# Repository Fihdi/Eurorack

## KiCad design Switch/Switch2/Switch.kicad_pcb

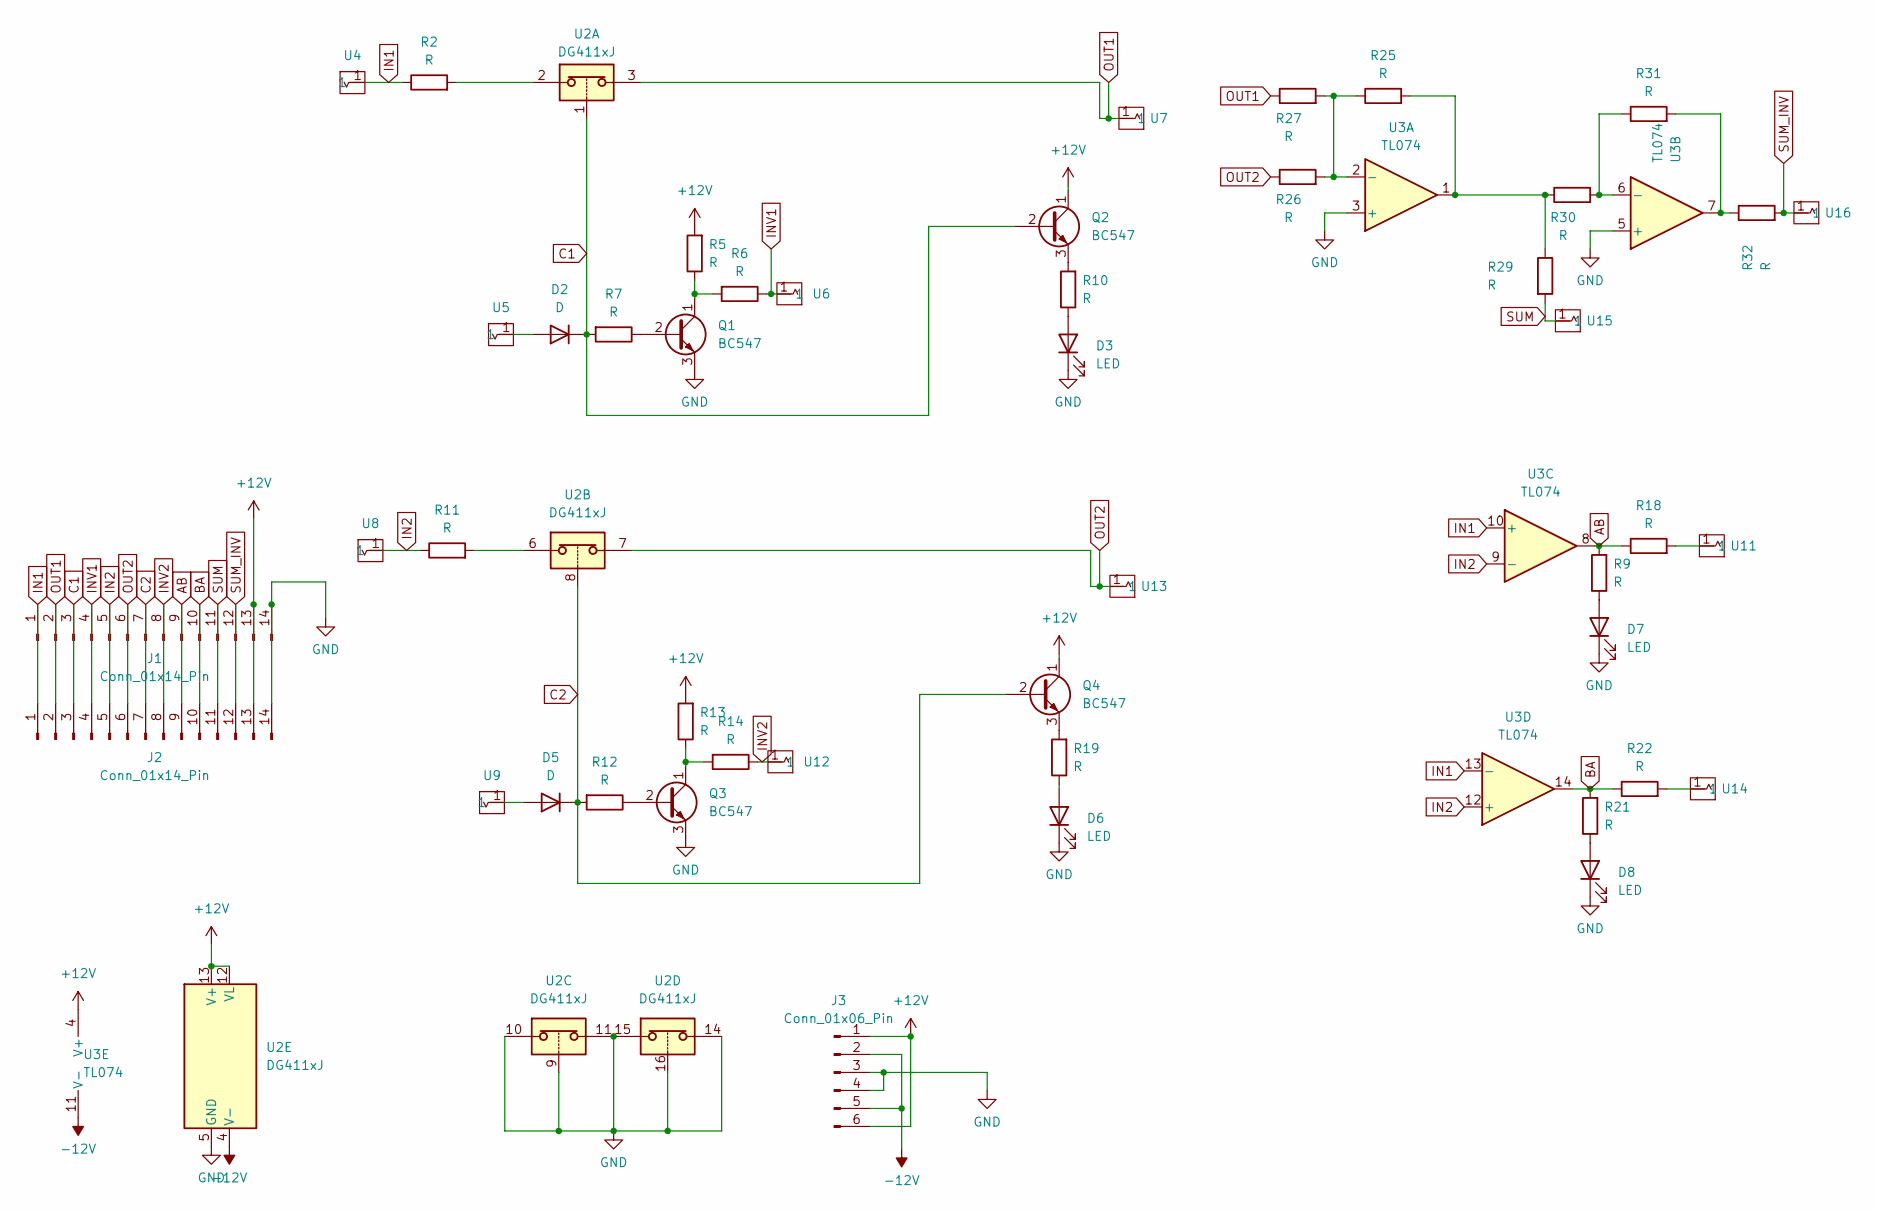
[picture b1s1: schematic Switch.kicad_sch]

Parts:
D2, D5: D; D_DO-34_SOD68_P5.08mm_Vertical_AnodeUp
D3, D6, D7, D8: LED; LED_D3.0mm
J1, J2: Conn_01x14_Pin; PinHeader_1x14_P2.54mm_Vertical
J3: Conn_01x06_Pin; PinHeader_1x06_P2.54mm_Vertical
Q1, Q2, Q3, Q4: BC547; TO-92L_Wide
R2, R5, R6, R7, R9, R10, R11, R12, R13, R14, R18, R19, R21, R22, R25, R26, R27, R29, R30, R31, R32: R; R_Axial_DIN0207_L6.3mm_D2.5mm_P7.62mm_Horizontal
U2: DG411xJ; DIP-16_W7.62mm
U3: TL074; DIP-14_W7.62mm_Socket
U4, U5, U6, U7, U8, U9, U11, U12, U13, U14, U15, U16: Aux_flush; aux_flush

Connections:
+12V: J1.13, J2.13, J3.1, J3.6, Q2.1 (C), Q4.1 (C), R5.2, R13.2, U2.12 (VL), U2.13 (V+), U3.4 (V+)
-12V: J3.2, J3.5, U2.4 (V-), U3.11 (V-)
AB: J1.9, J2.9, R9.2, R18.1, U3.8
BA: J1.10, J2.10, R21.2, R22.1, U3.14
C1: D2.1 (K), J1.3, J2.3, Q2.2 (B), R7.2, U2.1
C2: D5.1 (K), J1.7, J2.7, Q4.2 (B), R12.2, U2.8
GND: D3.1 (K), D6.1 (K), D7.1 (K), D8.1 (K), J1.14, J2.14, J3.3, J3.4, Q1.3 (E), Q3.3 (E), U2.5 (GND), U2.9, U2.10, U2.11, U2.14, U2.15, U2.16, U3.3 (+), U3.5 (+)
IN1: J1.1, J2.1, R2.1, U3.10 (+), U3.13 (-), U4.1
IN2: J1.5, J2.5, R11.1, U3.9 (-), U3.12 (+), U8.1
INV1: J1.4, J2.4, R6.1, U6.1
INV2: J1.8, J2.8, R14.1, U12.1
unnamed: D2.2 (A), U5.1
unnamed: D3.2 (A), R10.1
unnamed: D5.2 (A), U9.1
unnamed: D6.2 (A), R19.1
unnamed: D7.2 (A), R9.1
unnamed: D8.2 (A), R21.1
unnamed: Q1.2 (B), R7.1
unnamed: Q1.1 (C), R5.1, R6.2
unnamed: Q2.3 (E), R10.2
unnamed: Q3.2 (B), R12.1
unnamed: Q3.1 (C), R13.1, R14.2
unnamed: Q4.3 (E), R19.2
unnamed: R2.2, U2.2
unnamed: R11.2, U2.6
unnamed: R18.2, U11.1
unnamed: R22.2, U14.1
unnamed: R25.2, R29.1, R30.1, U3.1
unnamed: R31.2, R32.1, U3.7
unnamed: R25.1, R26.2, R27.2, U3.2 (-)
unnamed: R30.2, R31.1, U3.6 (-)
OUT1: J1.2, J2.2, R27.1, U2.3, U7.1
OUT2: J1.6, J2.6, R26.1, U2.7, U13.1
SUM: J1.11, J2.11, R29.2, U15.1
SUM_INV: J1.12, J2.12, R32.2, U16.1

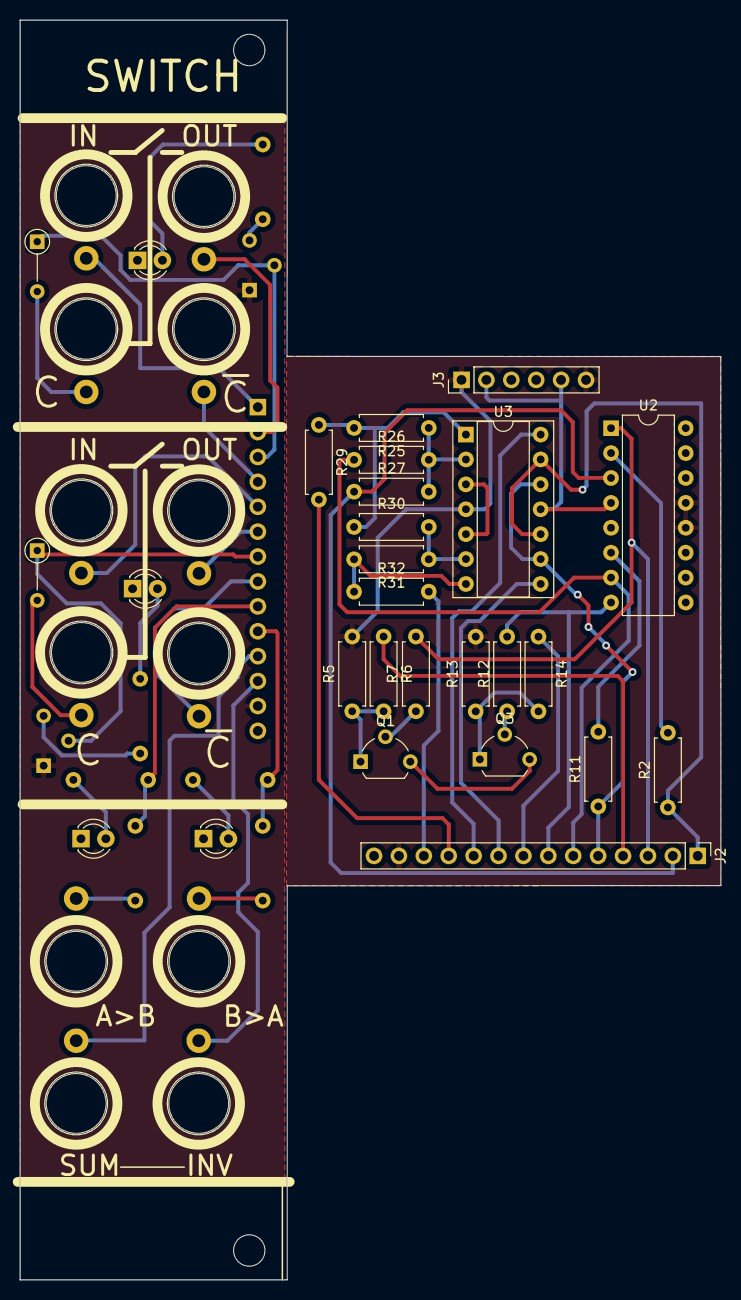
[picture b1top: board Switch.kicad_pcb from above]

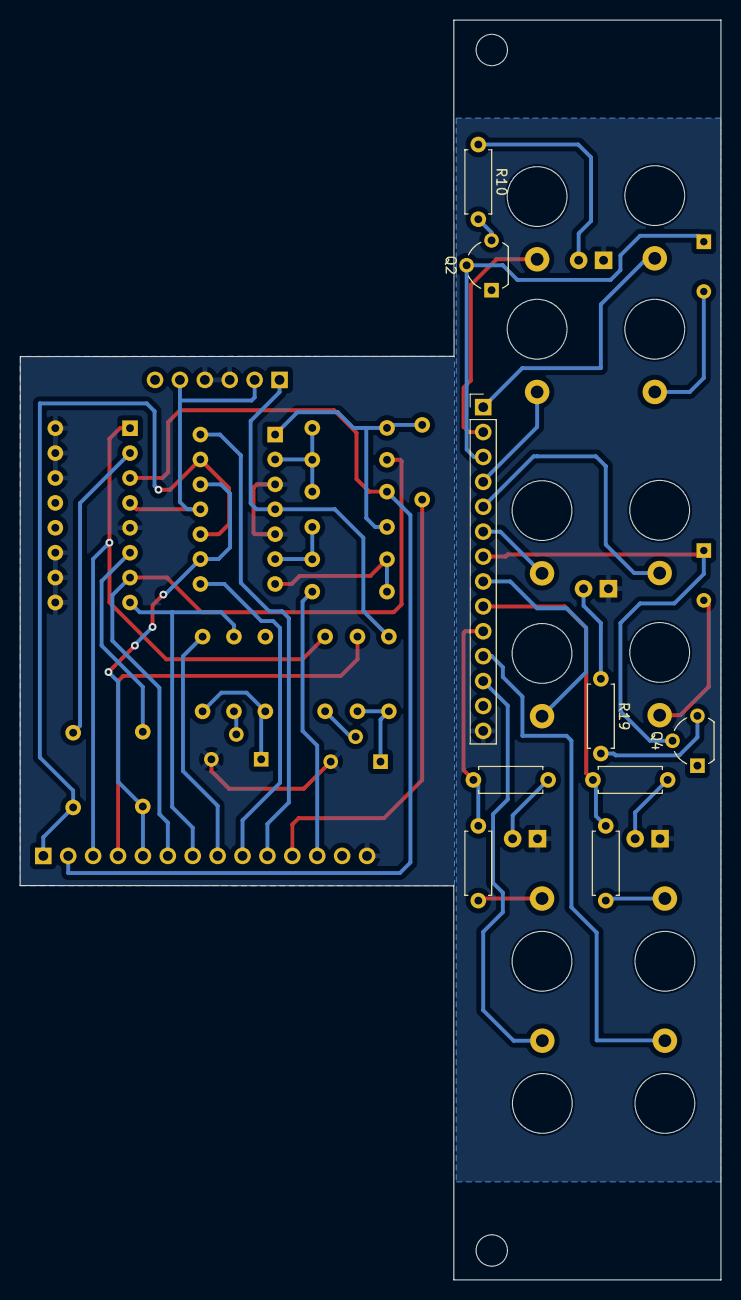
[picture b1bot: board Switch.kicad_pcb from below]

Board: 2 copper layers, 71.5 x 128.5 mm, 48 parts (9 on the bottom side), 35 nets.

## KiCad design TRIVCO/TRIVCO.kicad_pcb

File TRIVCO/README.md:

It is a beefed up relaxation oscillator using an inverting schmitt trigger. See: https://en.wikipedia.org/wiki/Relaxation_oscillator. The charging resistor has been replaced by an LM13700 trans-conductance amplifier (OTA), acting as a CCCS. The control voltages are summed through two inverting amplifiers with unity gain and sent to an exponential current converter that controls the OTA's output current (And thus the frequency). Tuning the exponential current converter is crucial to get proper Volt per Octave tracking.

The capacitor voltage is buffered and DC offset is removed (triangle/saw output), that voltage is compared to either ground or to an external voltage leveled to approx. 5V and buffered once again (pwm output).

The SYNCH input features a schmitt trigger input with small hysteresis (~100mV) to prevent spontaneous syncing from noise. For signals substantialy bigger than 100mV this schmitt trigger acts as a zero-crossing comparator; Whose output is fed to the schmitt trigger junction of the oscillator, achieving synchronisation by averaging the two schmitt triggers outputs together.

Minor issues:
-No trimpots for 1V/Oct tracking

-Triangle signal after the buffer is shifted up/down by the schmitt trigger for synchronisation -> comparator compares this signal to ground -> duty cylce is not 50% at default. This should be easily fixable by adding a decoupling cap in series to R14, or by bypassing the comparator alltogether and connecting the 100k resistor directly to the SYNCH input

-LED is mostly usless excpet when using the module as an LFO.

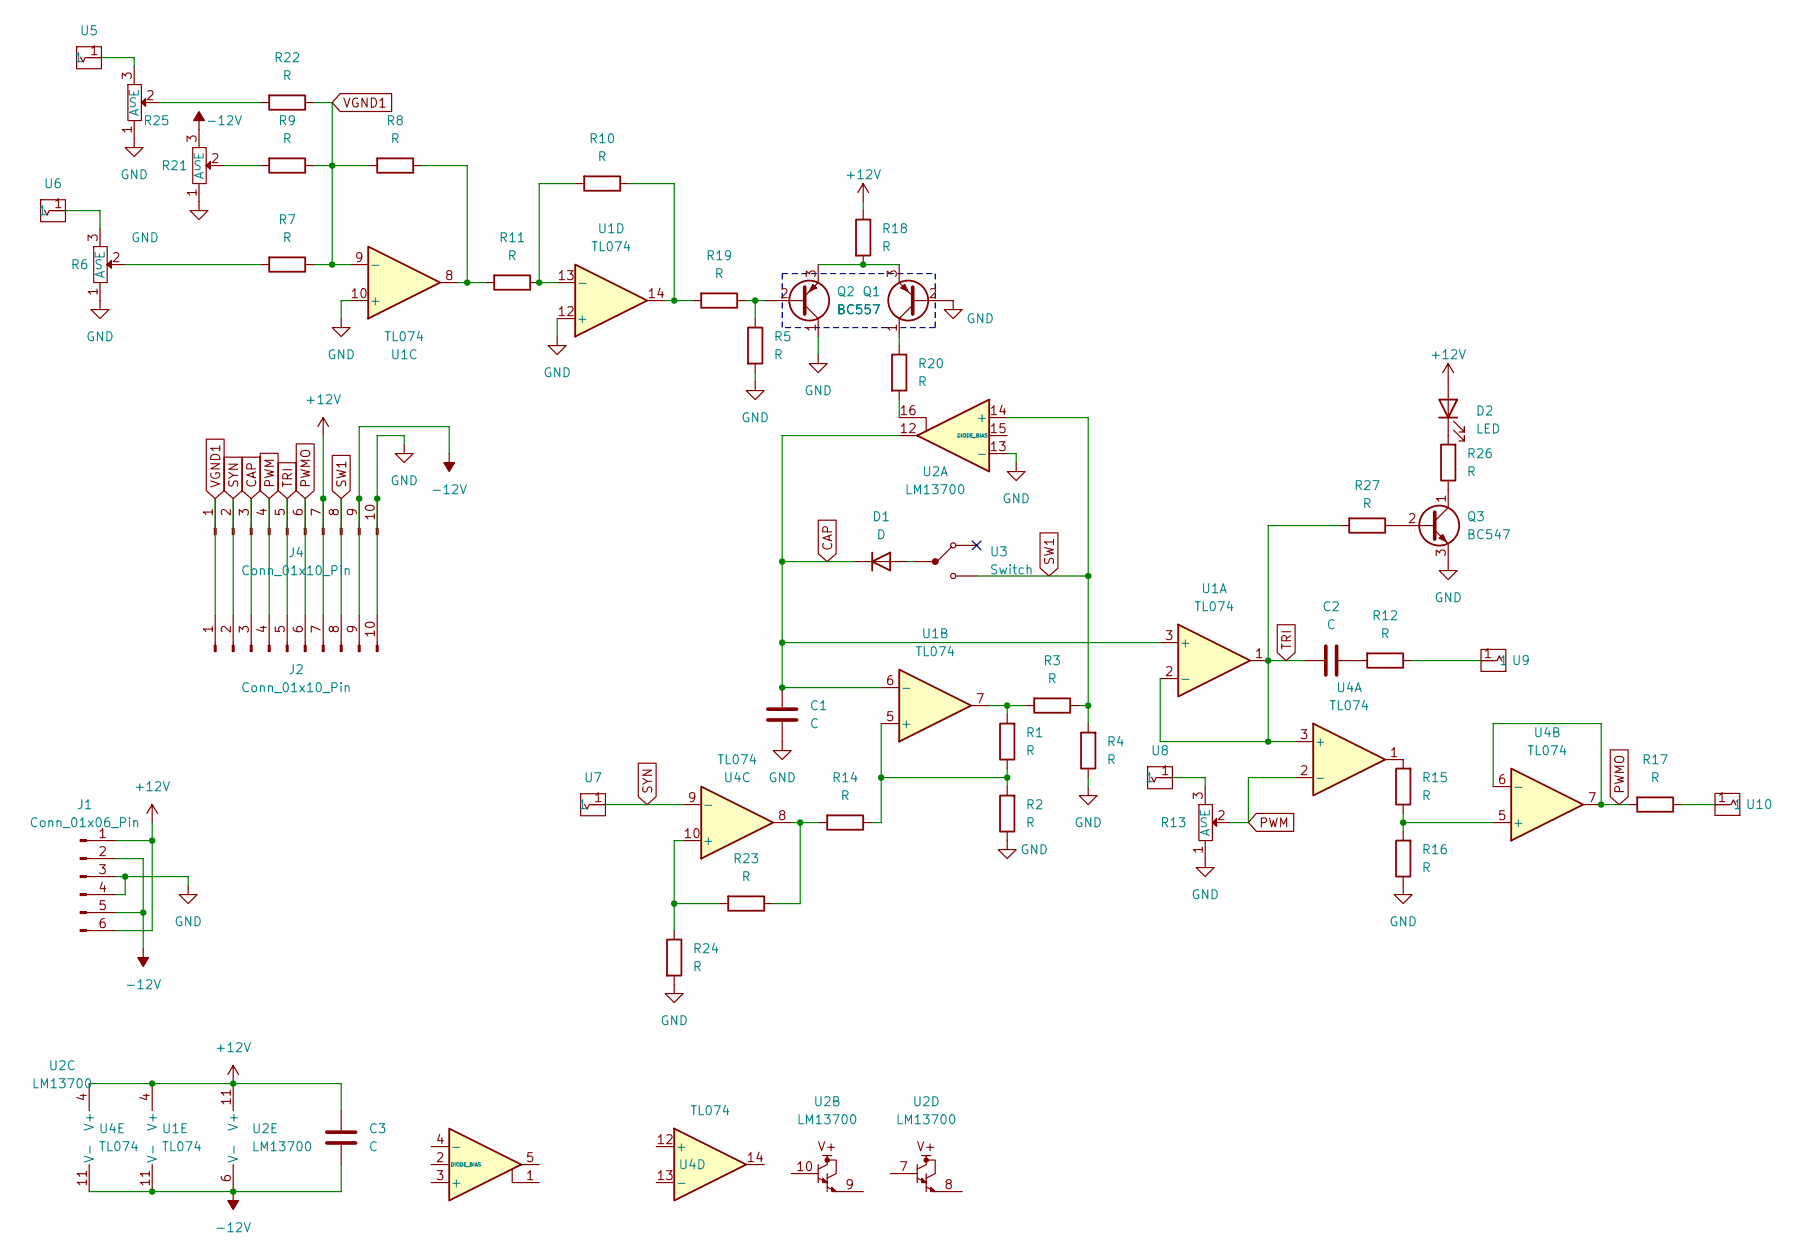
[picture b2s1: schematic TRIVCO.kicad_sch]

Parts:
C1, C2: C; C_Axial_L5.1mm_D3.1mm_P10.00mm_Horizontal
C3: C; C_Axial_L5.1mm_D3.1mm_P7.50mm_Horizontal
D1: D; D_A-405_P10.16mm_Horizontal
D2: LED; LED_D5.0mm
J1: Conn_01x06_Pin; PinHeader_1x06_P2.54mm_Vertical
J2, J4: Conn_01x10_Pin; PinHeader_1x10_P2.54mm_Vertical
Q1, Q2: BC557; TO-92L_Inline_Wide
Q3: BC547; TO-92L_Inline_Wide
R1, R2, R3, R4, R5, R7, R8, R9, R10, R11, R12, R14, R15, R16, R17, R18, R19, R20, R22, R23, R24, R26, R27: R; R_Axial_DIN0207_L6.3mm_D2.5mm_P10.16mm_Horizontal
R6, R13, R21, R25: AlpsPot
U1, U4: TL074; DIP-14_W7.62mm_Socket
U2: LM13700; DIP-16_W7.62mm_Socket
U3: Switch
U5, U6, U7, U8, U9, U10: Aux_flush; 3mm5 Mono Aux

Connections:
+12V: C3.1, D2.2 (A), J1.1, J1.6, J2.7, J4.7, R18.1, U1.4 (V+), U2.11 (V+), U4.4 (V+)
-12V: C3.2, J1.2, J1.5, J2.9, J4.9, R21.3 (E), U1.11 (V-), U2.6 (V-), U4.11 (V-)
CAP: C1.1, D1.1 (K), J2.3, J4.3, U1.3 (+), U1.6 (-), U2.12
GND: C1.2, J1.3, J1.4, J2.10, J4.10, Q1.2 (B), Q2.1 (C), Q3.3 (E), R2.1, R4.1, R5.2, R6.1 (A), R13.1 (A), R16.1, R21.1 (A), R24.2, R25.1 (A), U1.10 (+), U1.12 (+), U2.13 (-)
unnamed: C2.2, R12.2
unnamed: D1.2 (A), U3.2
unnamed: D2.1 (K), R26.2
unnamed: Q1.1 (C), R20.1
unnamed: Q1.3 (E), Q2.3 (E), R18.2
unnamed: Q2.2 (B), R5.1, R19.1
unnamed: Q3.2 (B), R27.1
unnamed: Q3.1 (C), R26.1
unnamed: R1.2, R3.2, U1.7
unnamed: R6.3 (E), U6.1
unnamed: R6.2 (S), R7.2
unnamed: R10.1, R19.2, U1.14
unnamed: R8.1, R11.2, U1.8
unnamed: R12.1, U9.1
unnamed: R13.3 (E), U8.1
unnamed: R14.2, R23.1, U4.8
unnamed: R15.2, U4.1
unnamed: R17.1, U10.1
unnamed: R20.2, U2.16
unnamed: R9.2, R21.2 (S)
unnamed: R25.3 (E), U5.1
unnamed: R22.2, R25.2 (S)
unnamed: R1.1, R2.2, R14.1, U1.5 (+)
unnamed: R10.2, R11.1, U1.13 (-)
unnamed: R15.1, R16.2, U4.5 (+)
unnamed: R23.2, R24.1, U4.10 (+)
PWM: J2.4, J4.4, R13.2 (S), U4.2 (-)
PWMO: J2.6, J4.6, R17.2, U4.6 (-), U4.7
SW1: J2.8, J4.8, R3.1, R4.2, U2.14 (+), U3.3
SYN: J2.2, J4.2, U4.9 (-), U7.1
TRI: C2.1, J2.5, J4.5, R27.2, U1.1, U1.2 (-), U4.3 (+)
VGND1: J2.1, J4.1, R7.1, R8.2, R9.1, R22.1, U1.9 (-)

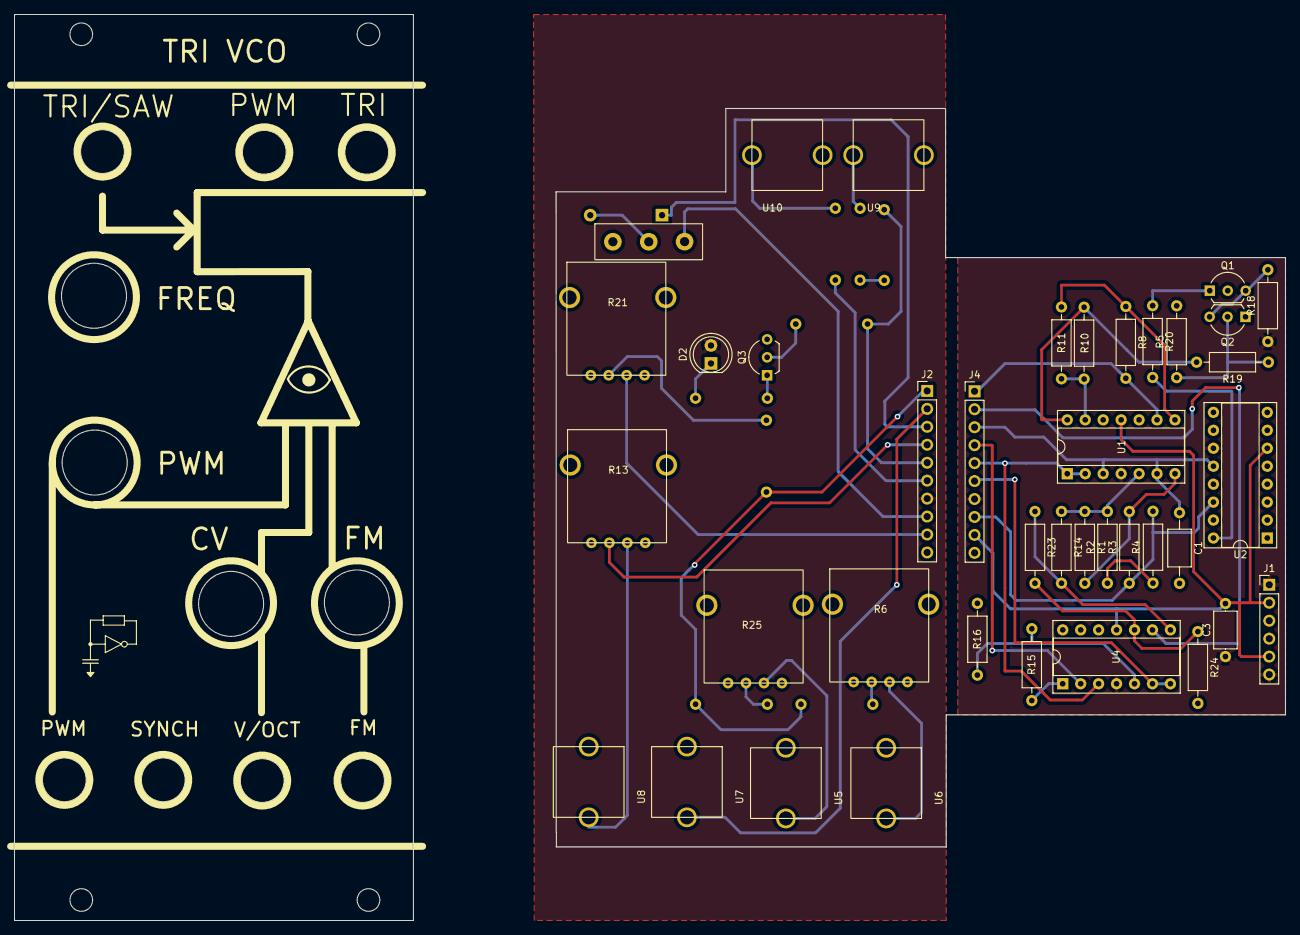
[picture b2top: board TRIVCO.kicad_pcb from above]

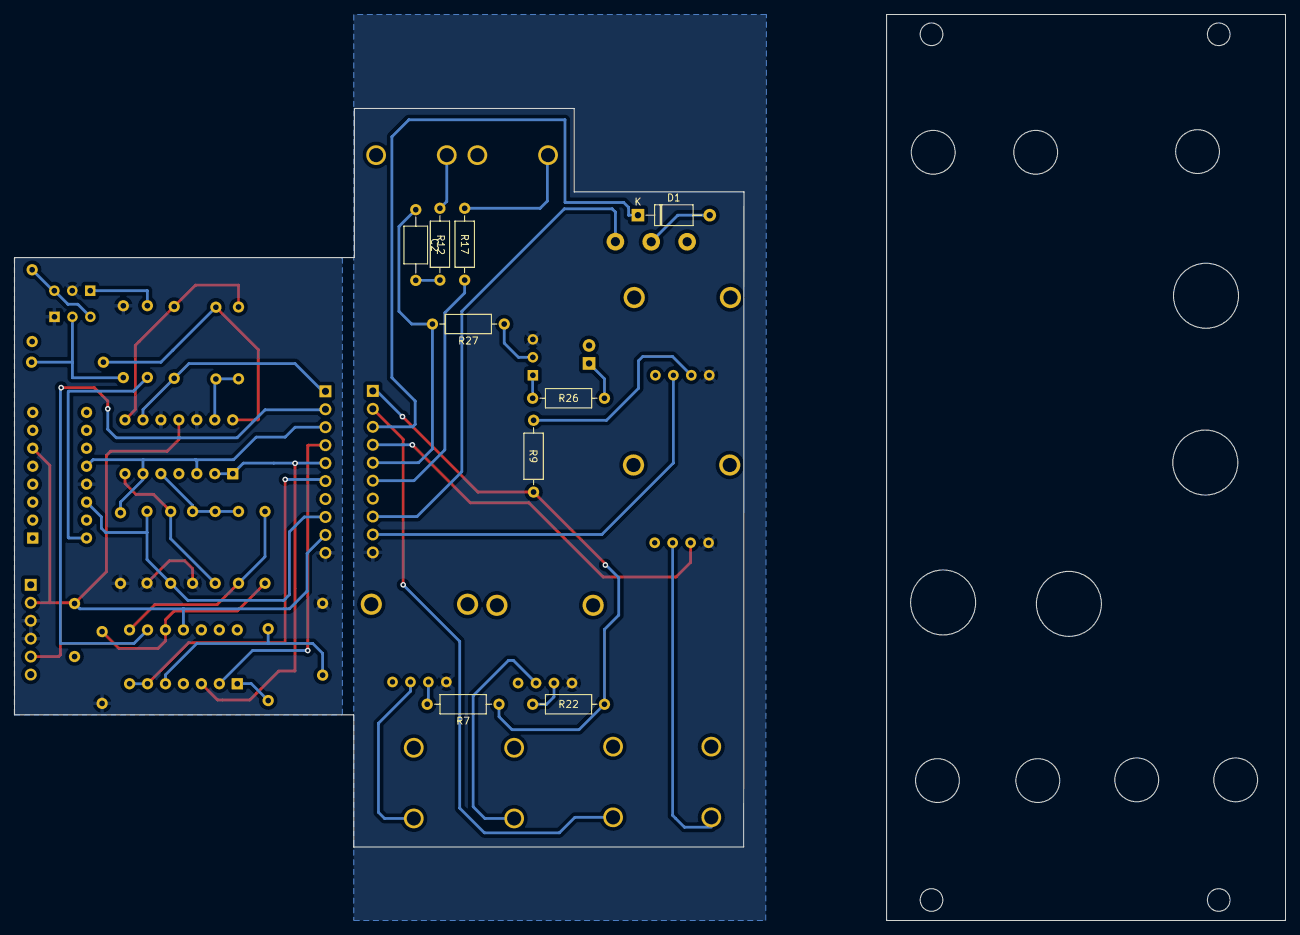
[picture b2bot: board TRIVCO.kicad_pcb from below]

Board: 2 copper layers, 103.2 x 104.5 mm, 48 parts (9 on the bottom side), 36 nets.

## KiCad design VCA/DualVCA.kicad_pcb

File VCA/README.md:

This module is rather bulky for what it can do, so I would not build this. Build the Crossfader module instead for two VCAs in one (plus features).
Forgot the Power Connections to the TL074

No LED!

No attenuator for CV

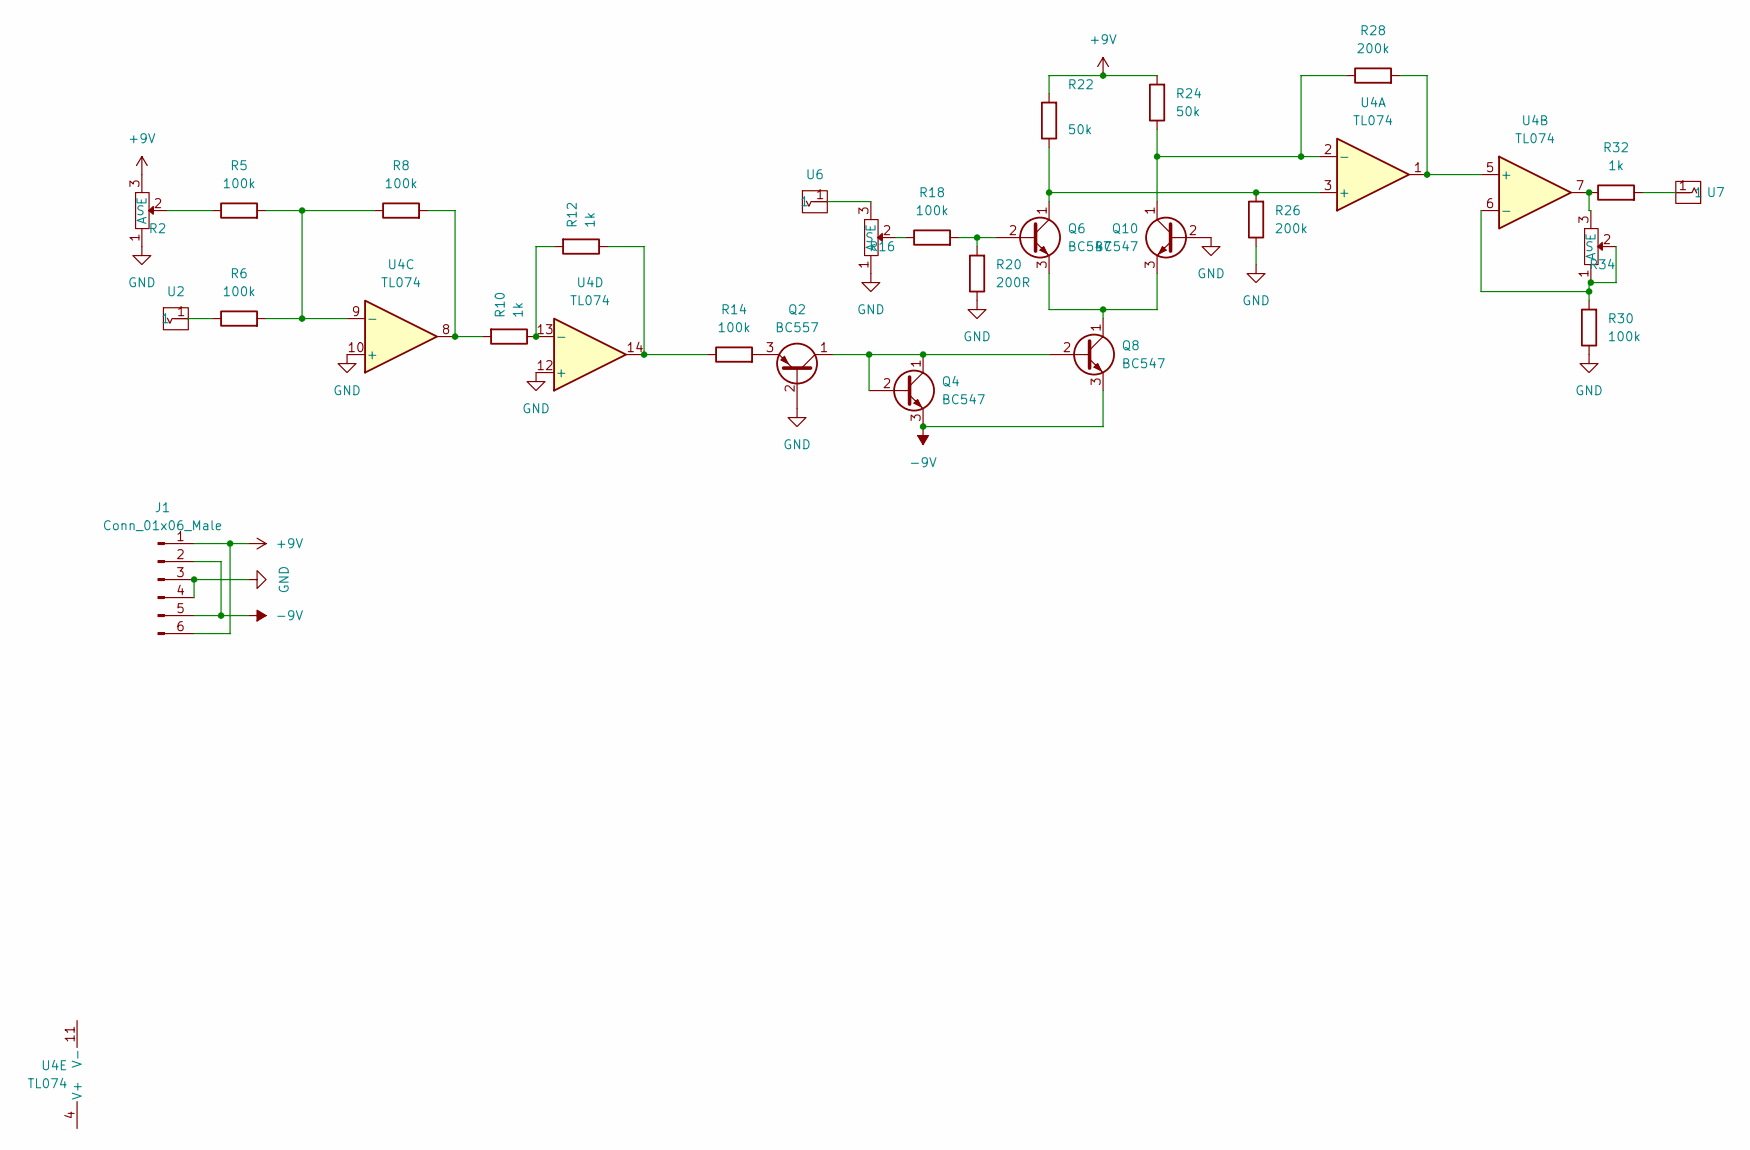
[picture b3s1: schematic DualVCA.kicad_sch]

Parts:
J1: Conn_01x06_Male
Q2: BC557; TO-92_Inline_Wide
Q4, Q6, Q8, Q10: BC547; TO-92_Inline_Wide
R2, R16, R34: AlpsPot
R5, R6, R8, R14, R18, R30: 100k; R_Axial_DIN0204_L3.6mm_D1.6mm_P7.62mm_Horizontal
R10, R12, R32: 1k; R_Axial_DIN0204_L3.6mm_D1.6mm_P7.62mm_Horizontal
R20: 200R; R_Axial_DIN0204_L3.6mm_D1.6mm_P7.62mm_Horizontal
R22, R24: 50k; R_Axial_DIN0204_L3.6mm_D1.6mm_P7.62mm_Horizontal
R26, R28: 200k; R_Axial_DIN0204_L3.6mm_D1.6mm_P7.62mm_Horizontal
U2, U6, U7: Aux_flush; aux_flush
U4: TL074; DIP-14_W7.62mm

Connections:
+9V: J1.1, J1.6, R2.3 (E), R22.2, R24.2
-9V: J1.2, J1.5, Q4.3 (E), Q8.3 (E)
GND: J1.3, J1.4, Q2.2 (B), Q10.2 (B), R2.1 (A), R16.1 (A), R20.1, R26.1, R30.1, U4.10 (+), U4.12 (+)
unnamed: Q2.1 (C), Q4.1 (C), Q4.2 (B), Q8.2 (B)
unnamed: Q2.3 (E), R14.2
unnamed: Q6.1 (C), R22.1, R26.2, U4.3 (+)
unnamed: Q6.2 (B), R18.2, R20.2
unnamed: Q10.1 (C), R24.1, R28.1, U4.2 (-)
unnamed: Q6.3 (E), Q8.1 (C), Q10.3 (E)
unnamed: R2.2 (S), R5.1
unnamed: R5.2, R6.2, R8.1, U4.9 (-)
unnamed: R6.1, U2.1
unnamed: R10.1, R12.2, U4.13 (-)
unnamed: R8.2, R10.2, U4.8
unnamed: R12.1, R14.1, U4.14
unnamed: R16.2 (S), R18.1
unnamed: R16.3 (E), U6.1
unnamed: R28.2, U4.1, U4.5 (+)
unnamed: R30.2, R34.1 (A), R34.2 (S), U4.6 (-)
unnamed: R32.1, R34.3 (E), U4.7
unnamed: R32.2, U7.1

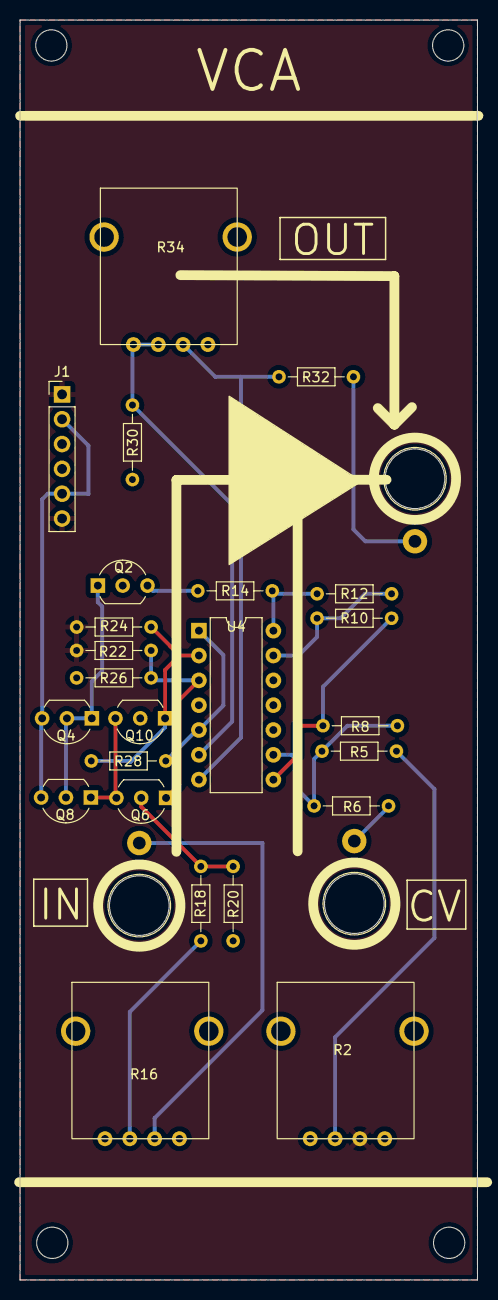
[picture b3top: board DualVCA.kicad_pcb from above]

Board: 2 copper layers, 46.8 x 128.9 mm, 27 parts (0 on the bottom side), 21 nets.

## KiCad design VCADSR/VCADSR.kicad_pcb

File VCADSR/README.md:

Voltage controlled Attack Decay Sustain Release Module.

Manual Trigger, Loop and x4 Switch. Rates for ADR and the level for Sustain can be controlled manually or by CV with onboard attenuaters
Tested this on breadboard and it works nicely.

Basic schematic inspired by Rene Schmitz. An RS flipflop and analog switches control the charge and discharge paths for the capacitor.
The way I made the circuit voltage controlled is by using current mirrors as VCRs, their job is to limit the current, and thus how fast the capacitor charges (or discharges). 
The "Q" output of the flipflop is responsible for the Attack. Q and the PNP current mirror is the sole path that the capacitor charges up. Since the control current of the mirror is linear, the current to the cap is constant, and the voltage charges linearly instead of logarithmically.

The two NPN current mirrors are used to drop the capacitors voltage, again linearly. One current mirror is used for the decay phase, the other for the release phase.

The PNP transistor before the decay current mirror cuts off the current flow when the voltage reaches Vsus + 500mV. The capacitor is thus held at this voltage and the circuit is in the sustain phase until the input gate dissapears. 

Once the input gate dissapears the current mirror for the release phase discharges the capacitor until 0V.

MOSFETS are used as AND gates to extract the phases of the circuit and indicated with LEDs.

The PCB is the only 4 layer PCB of my modules because the circuit is quiet big (or I am just terrible at routing), either way I would preferr the board(s) to be 2 layer and THT-only.

https://www.schmitzbits.de/adsr.html

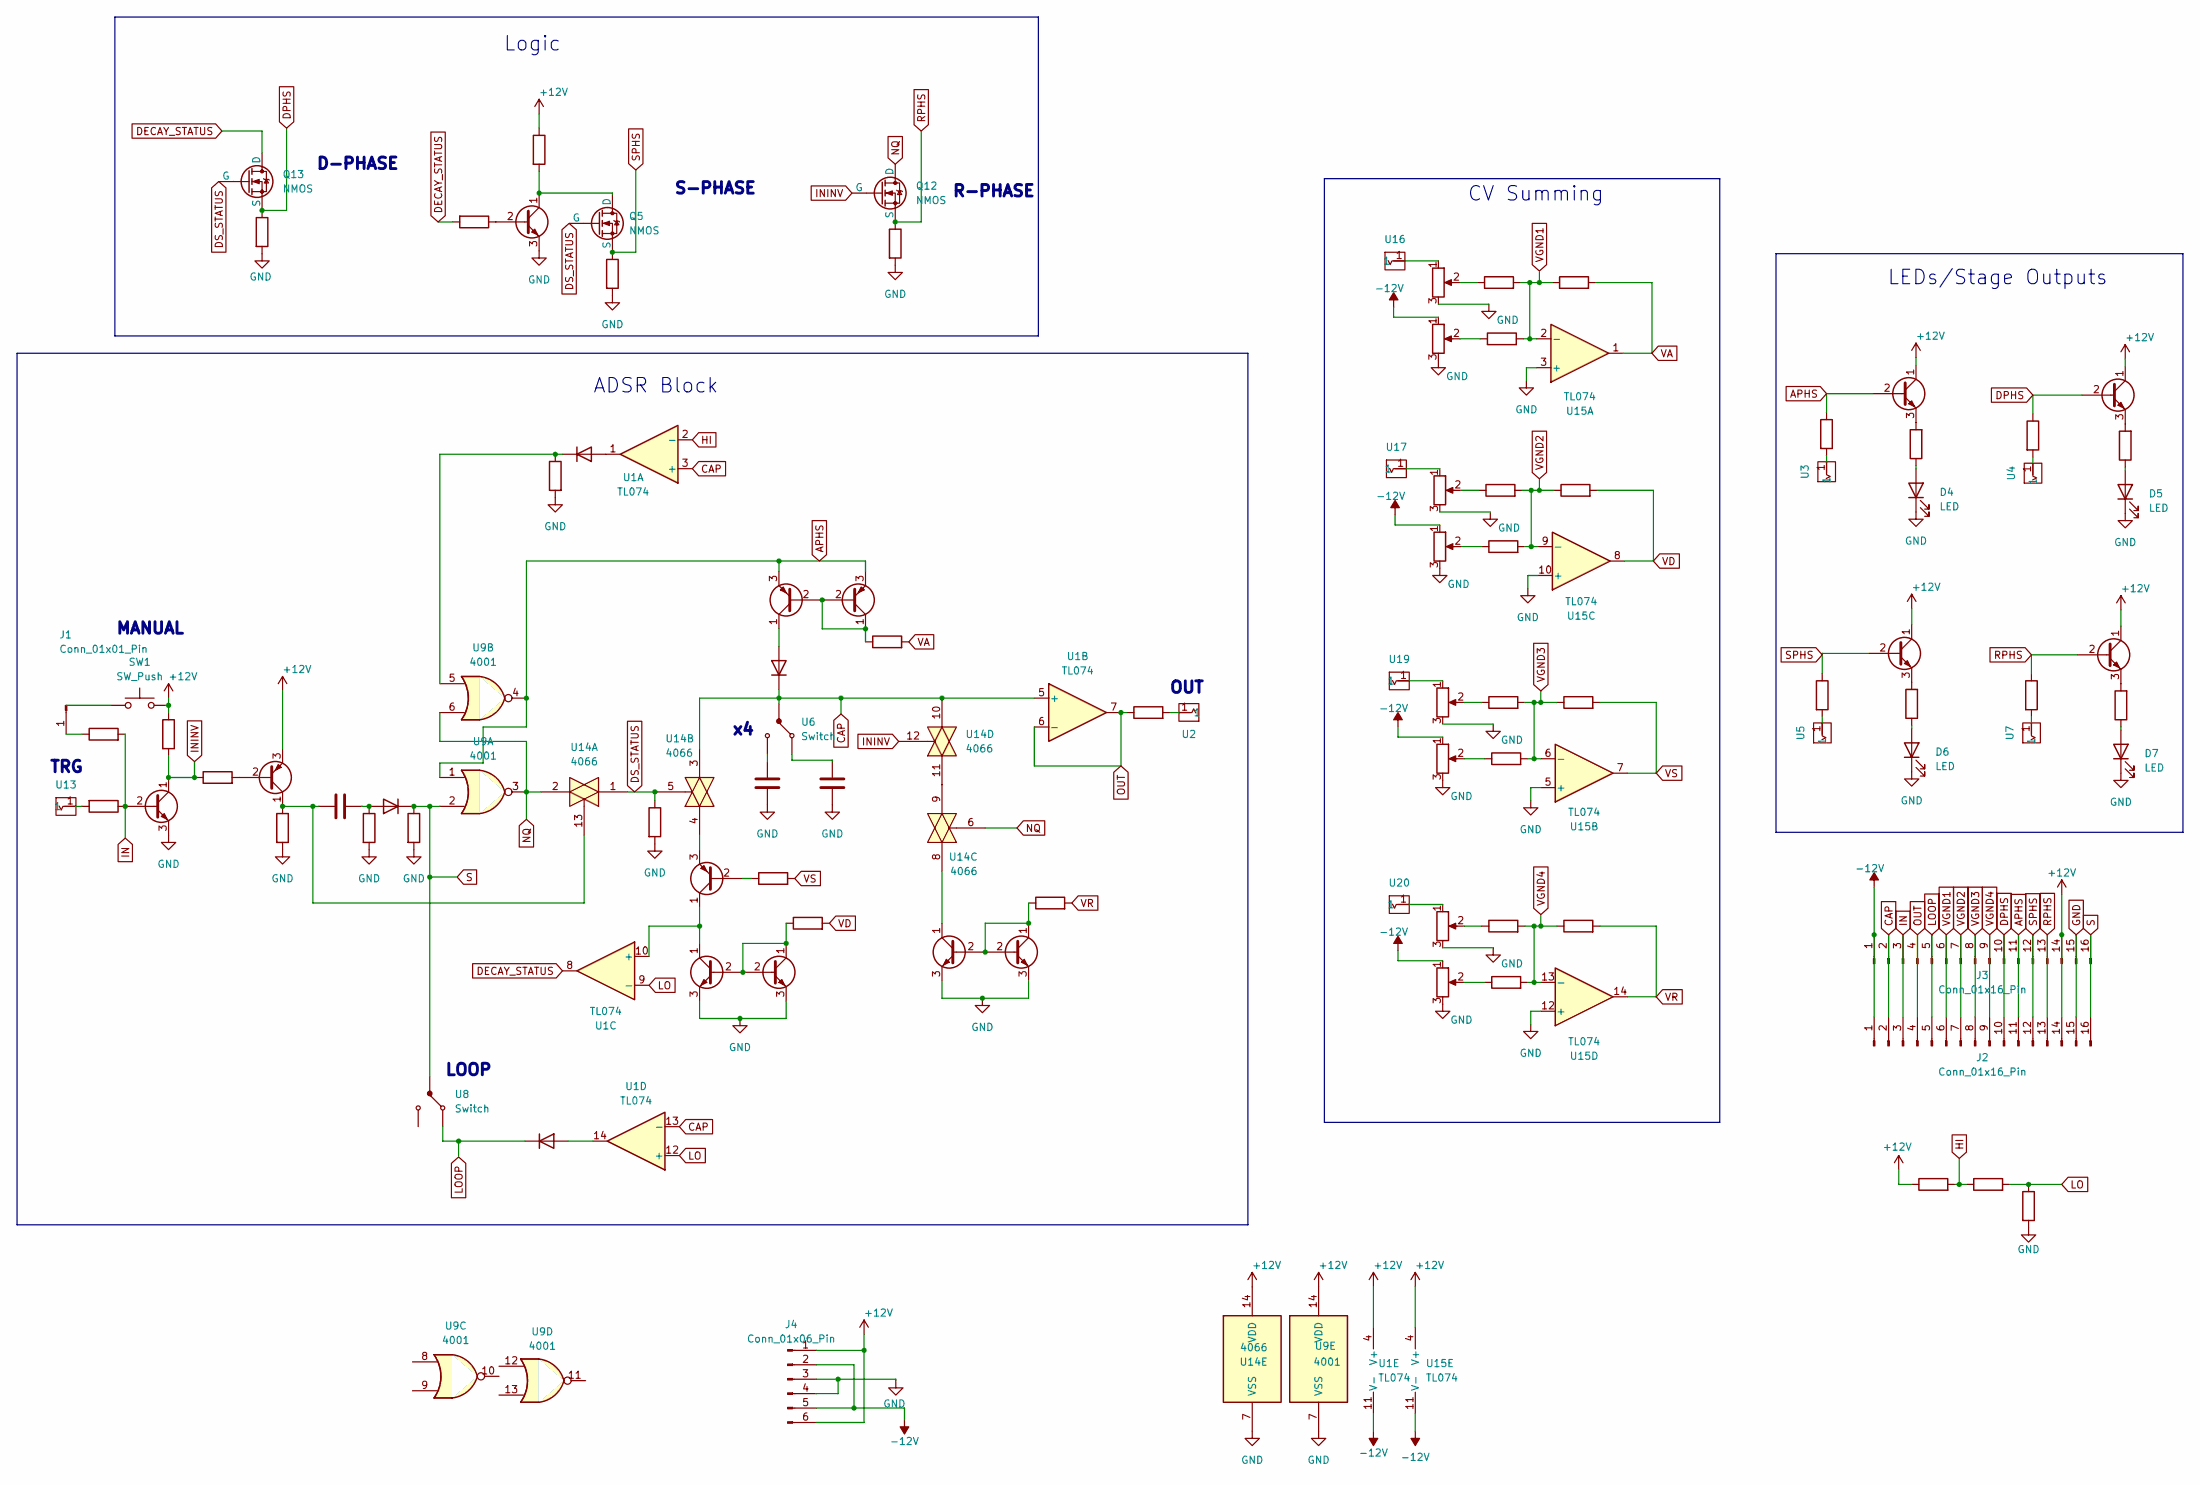
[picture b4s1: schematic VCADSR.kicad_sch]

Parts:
C1, C2, C3: C; C_Axial_L3.8mm_D2.6mm_P7.50mm_Horizontal
D1, D2, D3, D8: D; D_A-405_P5.08mm_Vertical_AnodeUp
D4, D5, D6, D7: LED; LED_D3.0mm
J1: Conn_01x01_Pin; PinHeader_1x01_P2.54mm_Vertical
J2, J3: Conn_01x16_Pin; PinHeader_1x16_P2.54mm_Vertical
J4: Conn_01x06_Pin; PinHeader_1x06_P2.54mm_Vertical
Q1, Q2, Q8, Q9: BC557; TO-92_Inline_Wide
Q3, Q4, Q6, Q7, Q10, Q11: BC547; TO-92_Inline_Wide
Q5, Q12, Q13: NMOS; TO-92_Inline_Wide
Q14, Q15, Q16, Q17: BC547; SOT-23
R1, R2, R3, R4, R5, R6, R7, R8, R9, R12, R13, R14, R15, R22, R23, R24, R25, R38, R39, R40, R41, R42, R43, R44, R45, R46, R47, R48, R49, R50, R51, R52, R53, R54, R55, R56, R57, R58: R; R_Axial_DIN0204_L3.6mm_D1.6mm_P7.62mm_Horizontal
R11, R17, R19, R21: R; R_1206_3216Metric
RV6, RV7, RV8, RV9, RV10, RV11, RV12, RV13: R_Potentiometer; AlpsPot
SW1: SW_Push; Push_Flush
U1, U15: TL074; DIP-14_W7.62mm_Socket
U2, U3, U4, U5, U7, U13, U16, U17, U19, U20: Aux_flush; aux_flush
U6, U8: Switch; SPDT Mini
U9: 4001; DIP-14_W7.62mm
U14: 4066; DIP-14_W7.62mm_Socket

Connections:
+12V: J2.14, J3.14, J4.1, J4.6, Q8.3 (E), Q14.1 (C), Q15.1 (C), Q16.1 (C), Q17.1 (C), R7.1, R23.1, R39.1, SW1.2, U1.4 (V+), U9.14 (VDD), U14.14 (VDD), U15.4 (V+)
-12V: J2.1, J3.1, J4.2, J4.5, RV7.1, RV9.1, RV11.1, RV13.1, U1.11 (V-), U15.11 (V-)
APHS: J2.11, J3.11, Q1.3 (E), Q2.3 (E), Q14.2 (B), R9.1, U9.1, U9.4
CAP: D1.1 (K), J2.2, J3.2, U1.3 (+), U1.5 (+), U1.13 (-), U6.2, U14.3, U14.10
DECAY_STATUS: Q13.1 (D), R6.2, U1.8
DPHS: J2.10, J3.10, Q13.3 (S), Q15.2 (B), R12.1, R13.1
DS_STATUS: Q5.2 (G), Q13.2 (G), R44.1, U14.1, U14.5
GND: C1.1, C2.1, D4.1 (K), D5.1 (K), D6.1 (K), D7.1 (K), J2.15, J3.15, J4.3, J4.4, Q3.3 (E), Q4.3 (E), Q6.3 (E), Q7.3 (E), Q10.3 (E), Q11.3 (E), R2.2, R8.2, R12.2, R14.2, R25.2, R41.2, R42.2, R43.2, R44.2, RV6.3, RV7.3, RV8.3, RV9.3, RV10.3, RV11.3, RV12.3, RV13.3, U9.7 (VSS), U14.7 (VSS), U15.3 (+), U15.5 (+), U15.10 (+), U15.12 (+)
HI: R23.2, R24.1, U1.2 (-)
IN: J2.3, J3.3, Q7.2 (B), R5.2, R38.1
LO: R24.2, R25.1, U1.9 (-), U1.12 (+)
LOOP: D3.1 (K), J2.5, J3.5, U8.1
NQ: Q12.1 (D), U9.3, U9.6, U14.2, U14.6
unnamed: C1.2, U6.1
unnamed: C2.2, U6.3
unnamed: D1.2 (A), Q2.1 (C)
unnamed: D2.2 (A), U1.1
unnamed: D2.1 (K), R2.1, U9.5
unnamed: D3.2 (A), U1.14
unnamed: D4.2 (A), R11.1
unnamed: D5.2 (A), R17.1
unnamed: D6.2 (A), R19.1
unnamed: D7.2 (A), R21.1
unnamed: C3.2, D8.2 (A), R42.1
unnamed: J1.1, R5.1
unnamed: Q1.1 (C), Q1.2 (B), Q2.2 (B), R1.1
unnamed: Q3.2 (B), Q4.1 (C), Q4.2 (B), R3.1
unnamed: Q3.1 (C), U14.8
unnamed: Q5.1 (D), Q6.1 (C), R7.2
unnamed: Q6.2 (B), R6.1
unnamed: Q8.2 (B), R40.2
unnamed: C3.1, Q8.1 (C), R41.1, U14.13
unnamed: Q9.2 (B), R45.1
unnamed: Q9.3 (E), U14.4
unnamed: Q10.1 (C), Q10.2 (B), Q11.2 (B), R49.1
unnamed: Q9.1 (C), Q11.1 (C), U1.10 (+)
unnamed: Q7.1 (C), Q12.2 (G), R39.2, R40.1, U14.12
unnamed: Q14.3 (E), R11.2
unnamed: Q15.3 (E), R17.2
unnamed: Q16.3 (E), R19.2
unnamed: Q17.3 (E), R21.2
unnamed: R4.2, U2.1
unnamed: R9.2, U3.1
unnamed: R13.2, U4.1
unnamed: R15.2, U5.1
unnamed: R22.2, U7.1
unnamed: R38.2, U13.1
unnamed: R46.1, RV7.2
unnamed: R48.1, RV6.2
unnamed: R50.1, RV8.2
unnamed: R51.1, RV9.2
unnamed: R53.1, RV10.2
unnamed: R54.1, RV12.2
unnamed: R55.1, RV11.2
unnamed: R56.1, RV13.2
unnamed: RV6.1, U16.1
unnamed: RV8.1, U17.1
unnamed: RV10.1, U19.1
unnamed: RV12.1, U20.1
unnamed: U14.9, U14.11
OUT: J2.4, J3.4, R4.1, U1.6 (-), U1.7
RPHS: J2.13, J3.13, Q12.3 (S), Q17.2 (B), R14.1, R22.1
S: D8.1 (K), J2.16, J3.16, R43.1, U8.2, U9.2
SPHS: J2.12, J3.12, Q5.3 (S), Q16.2 (B), R8.1, R15.1
VA: R1.2, R47.2, U15.1
VD: R49.2, R52.2, U15.8
VGND1: J2.6, J3.6, R46.2, R47.1, R48.2, U15.2 (-)
VGND2: J2.7, J3.7, R50.2, R51.2, R52.1, U15.9 (-)
VGND3: J2.8, J3.8, R53.2, R55.2, R57.1, U15.6 (-)
VGND4: J2.9, J3.9, R54.2, R56.2, R58.1, U15.13 (-)
VR: R3.2, R58.2, U15.14
VS: R45.2, R57.2, U15.7

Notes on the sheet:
R-PHASE
Logic
MANUAL
D-PHASE
LOOP
TRG
CV Summing
S-PHASE
LEDs/Stage Outputs
OUT
ADSR Block
